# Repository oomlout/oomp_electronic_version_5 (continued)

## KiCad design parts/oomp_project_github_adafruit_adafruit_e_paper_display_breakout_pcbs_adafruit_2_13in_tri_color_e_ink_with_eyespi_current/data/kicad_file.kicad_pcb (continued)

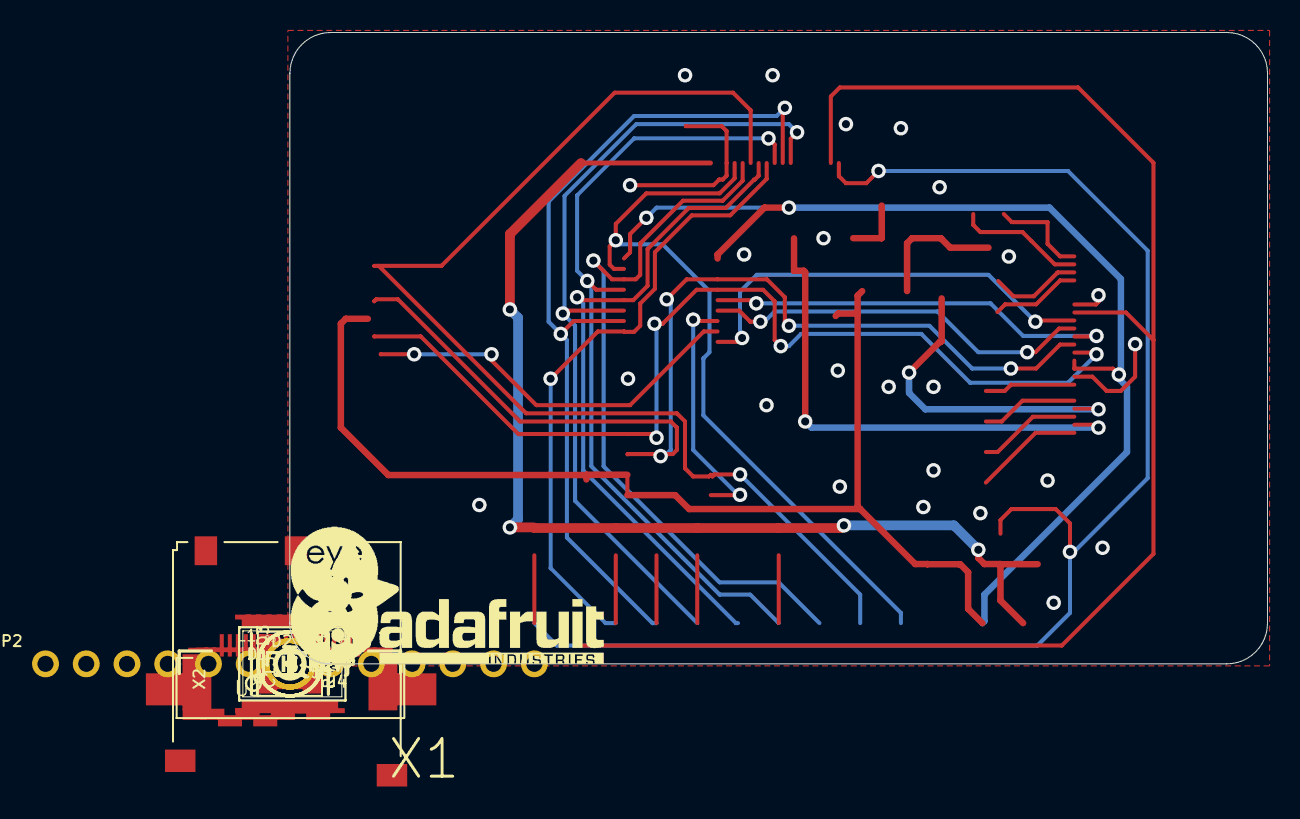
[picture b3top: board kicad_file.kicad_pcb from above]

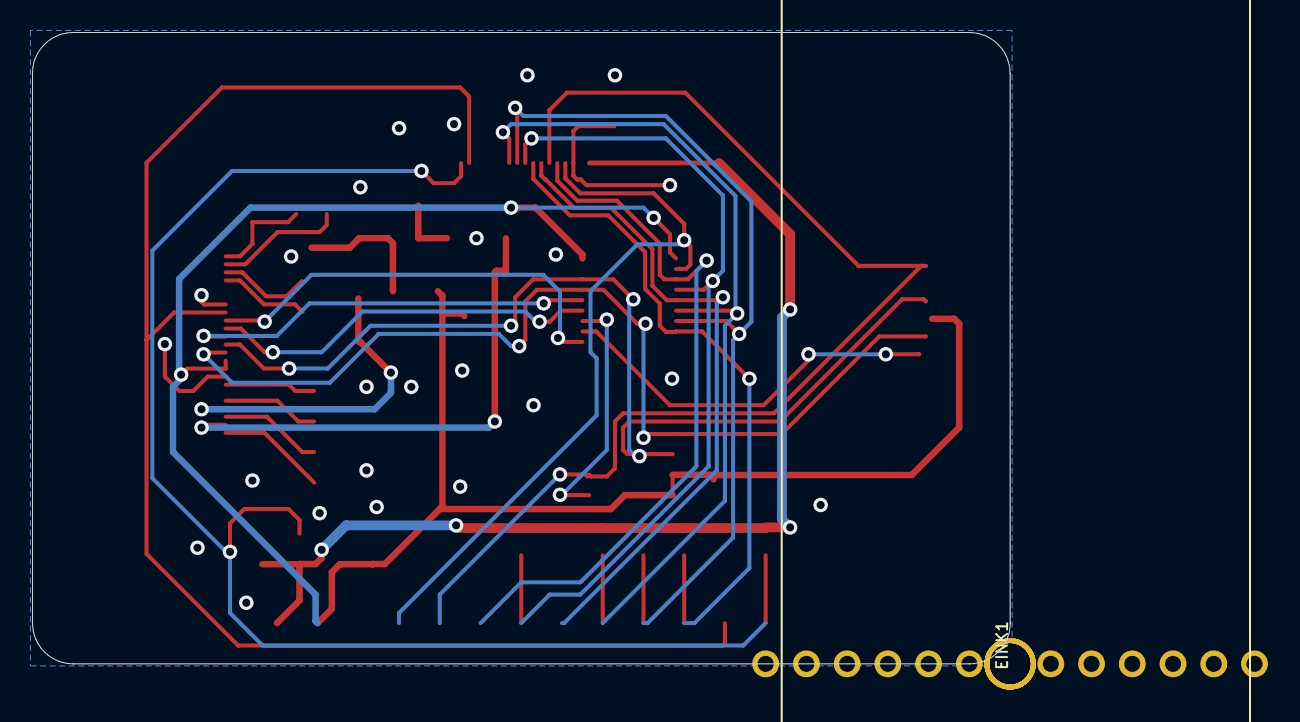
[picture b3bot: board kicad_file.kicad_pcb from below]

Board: 2 copper layers, 61.0 x 39.4 mm, 71 parts (16 on the bottom side), 32 nets.

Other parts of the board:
PLABEL0: PLABEL0
PLABEL1: PLABEL1
PLABEL2: PLABEL2
PLABEL3: PLABEL3
PLABEL4: PLABEL4
PLABEL5: PLABEL5
PLABEL6: PLABEL6
PLABEL7: PLABEL7
PLABEL8: PLABEL8
PLABEL9: PLABEL9
PLABEL10: PLABEL10
PLABEL11: PLABEL11
PLABEL12: PLABEL12
PLABEL13: PLABEL13
PLABEL14: PLABEL14
PLABEL15: PLABEL15
PLABEL16: PLABEL16
PLABEL17: PLABEL17
PLABEL18: PLABEL18
PLABEL19: PLABEL19
PLABEL20: PLABEL20
PLABEL21: PLABEL21
PLABEL22: PLABEL22
PLABEL23: PLABEL23
PLABEL24: PLABEL24
PLABEL25: PLABEL25
PLABEL26: PLABEL26
PLABEL27: PLABEL27
PLABEL28: PLABEL28
PLABEL29: PLABEL29
U$9: PCBFEAT-REV-040
U$28: ADAFRUIT_TEXT_20MM
U$35: EYESPI_MINI_LOGO

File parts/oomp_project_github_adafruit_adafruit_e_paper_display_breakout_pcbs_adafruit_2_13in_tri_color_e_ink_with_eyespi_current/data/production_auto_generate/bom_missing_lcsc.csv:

Designator,Comment,Footprint,OOMP ID,Reason
C5,10uF/16V,Adafruit 2.13in Tri-Color eInk with EYESPI-import-fps:0805-NO,electronic_capacitor_0805_10_micro_farad,No verified LCSC part number
C15,10uF/16V,Adafruit 2.13in Tri-Color eInk with EYESPI-import-fps:0805-NO,electronic_capacitor_0805_10_micro_farad,No verified LCSC part number
C20,10uF/16V,Adafruit 2.13in Tri-Color eInk with EYESPI-import-fps:0805-NO,electronic_capacitor_0805_10_micro_farad,No verified LCSC part number
C21,10uF/16V,Adafruit 2.13in Tri-Color eInk with EYESPI-import-fps:0805-NO,electronic_capacitor_0805_10_micro_farad,No verified LCSC part number
D1,MBR0540,Adafruit 2.13in Tri-Color eInk with EYESPI-import-fps:SOD-123,,No verified LCSC part number
D2,MBR0540,Adafruit 2.13in Tri-Color eInk with EYESPI-import-fps:SOD-123,,No verified LCSC part number
D3,MBR0540,Adafruit 2.13in Tri-Color eInk with EYESPI-import-fps:SOD-123,,No verified LCSC part number
EINK1,EINK_24PIN_213IN,Adafruit 2.13in Tri-Color eInk with EYESPI-import-fps:EINK_213IN_104X212,,No verified LCSC part number
L1,10uH,Adafruit 2.13in Tri-Color eInk with EYESPI-import-fps:INDUCTOR_4X4MM_NR401,,No verified LCSC part number
PLABEL0,,Adafruit 2.13in Tri-Color eInk with EYESPI-import-fps:PLABEL0,,No verified LCSC part number
PLABEL1,,Adafruit 2.13in Tri-Color eInk with EYESPI-import-fps:PLABEL1,,No verified LCSC part number
PLABEL2,,Adafruit 2.13in Tri-Color eInk with EYESPI-import-fps:PLABEL2,,No verified LCSC part number
PLABEL3,,Adafruit 2.13in Tri-Color eInk with EYESPI-import-fps:PLABEL3,,No verified LCSC part number
PLABEL4,,Adafruit 2.13in Tri-Color eInk with EYESPI-import-fps:PLABEL4,,No verified LCSC part number
PLABEL5,,Adafruit 2.13in Tri-Color eInk with EYESPI-import-fps:PLABEL5,,No verified LCSC part number
PLABEL6,,Adafruit 2.13in Tri-Color eInk with EYESPI-import-fps:PLABEL6,,No verified LCSC part number
PLABEL7,,Adafruit 2.13in Tri-Color eInk with EYESPI-import-fps:PLABEL7,,No verified LCSC part number
PLABEL8,,Adafruit 2.13in Tri-Color eInk with EYESPI-import-fps:PLABEL8,,No verified LCSC part number
PLABEL9,,Adafruit 2.13in Tri-Color eInk with EYESPI-import-fps:PLABEL9,,No verified LCSC part number
PLABEL10,,Adafruit 2.13in Tri-Color eInk with EYESPI-import-fps:PLABEL10,,No verified LCSC part number
PLABEL11,,Adafruit 2.13in Tri-Color eInk with EYESPI-import-fps:PLABEL11,,No verified LCSC part number
PLABEL12,,Adafruit 2.13in Tri-Color eInk with EYESPI-import-fps:PLABEL12,,No verified LCSC part number
PLABEL13,,Adafruit 2.13in Tri-Color eInk with EYESPI-import-fps:PLABEL13,,No verified LCSC part number
PLABEL14,,Adafruit 2.13in Tri-Color eInk with EYESPI-import-fps:PLABEL14,,No verified LCSC part number
PLABEL15,,Adafruit 2.13in Tri-Color eInk with EYESPI-import-fps:PLABEL15,,No verified LCSC part number
PLABEL16,,Adafruit 2.13in Tri-Color eInk with EYESPI-import-fps:PLABEL16,,No verified LCSC part number
PLABEL17,,Adafruit 2.13in Tri-Color eInk with EYESPI-import-fps:PLABEL17,,No verified LCSC part number
PLABEL18,,Adafruit 2.13in Tri-Color eInk with EYESPI-import-fps:PLABEL18,,No verified LCSC part number
PLABEL19,,Adafruit 2.13in Tri-Color eInk with EYESPI-import-fps:PLABEL19,,No verified LCSC part number
PLABEL20,,Adafruit 2.13in Tri-Color eInk with EYESPI-import-fps:PLABEL20,,No verified LCSC part number
PLABEL21,,Adafruit 2.13in Tri-Color eInk with EYESPI-import-fps:PLABEL21,,No verified LCSC part number
PLABEL22,,Adafruit 2.13in Tri-Color eInk with EYESPI-import-fps:PLABEL22,,No verified LCSC part number
PLABEL23,,Adafruit 2.13in Tri-Color eInk with EYESPI-import-fps:PLABEL23,,No verified LCSC part number
PLABEL24,,Adafruit 2.13in Tri-Color eInk with EYESPI-import-fps:PLABEL24,,No verified LCSC part number
PLABEL25,,Adafruit 2.13in Tri-Color eInk with EYESPI-import-fps:PLABEL25,,No verified LCSC part number
PLABEL26,,Adafruit 2.13in Tri-Color eInk with EYESPI-import-fps:PLABEL26,,No verified LCSC part number
PLABEL27,,Adafruit 2.13in Tri-Color eInk with EYESPI-import-fps:PLABEL27,,No verified LCSC part number
PLABEL28,,Adafruit 2.13in Tri-Color eInk with EYESPI-import-fps:PLABEL28,,No verified LCSC part number
PLABEL29,,Adafruit 2.13in Tri-Color eInk with EYESPI-import-fps:PLABEL29,,No verified LCSC part number
Q5,IRLML0100,Adafruit 2.13in Tri-Color eInk with EYESPI-import-fps:SOT23-3,,No verified LCSC part number
R4,0.47ohm,Adafruit 2.13in Tri-Color eInk with EYESPI-import-fps:0603-NO,,No verified LCSC part number
U1,74LVC245,Adafruit 2.13in Tri-Color eInk with EYESPI-import-fps:TSSOP20,,No verified LCSC part number
U2,AP2127K-3.3,Adafruit 2.13in Tri-Color eInk with EYESPI-import-fps:SOT23-5,,No verified LCSC part number
U4,23K640-I/SN,Adafruit 2.13in Tri-Color eInk with EYESPI-import-fps:SOIC8_150MIL,,No verified LCSC part number
U$9,,Adafruit 2.13in Tri-Color eInk with EYESPI-import-fps:PCBFEAT-REV-040,,No verified LCSC part number
U$28,,Adafruit 2.13in Tri-Color eInk with EYESPI-import-fps:ADAFRUIT_TEXT_20MM,,No verified LCSC part number
U$35,,Adafruit 2.13in Tri-Color eInk with EYESPI-import-fps:EYESPI_MINI_LOGO,,No verified LCSC part number
X1,EYE_SPI_DISPLAY_FLIP,Adafruit 2.13in Tri-Color eInk with EYESPI-import-fps:EYE_SPI_DISPLAY_BOTCONTACT,,No verified LCSC part number
X2,MICROSD,Adafruit 2.13in Tri-Color eInk with EYESPI-import-fps:MICROSD,,No verified LCSC part number
